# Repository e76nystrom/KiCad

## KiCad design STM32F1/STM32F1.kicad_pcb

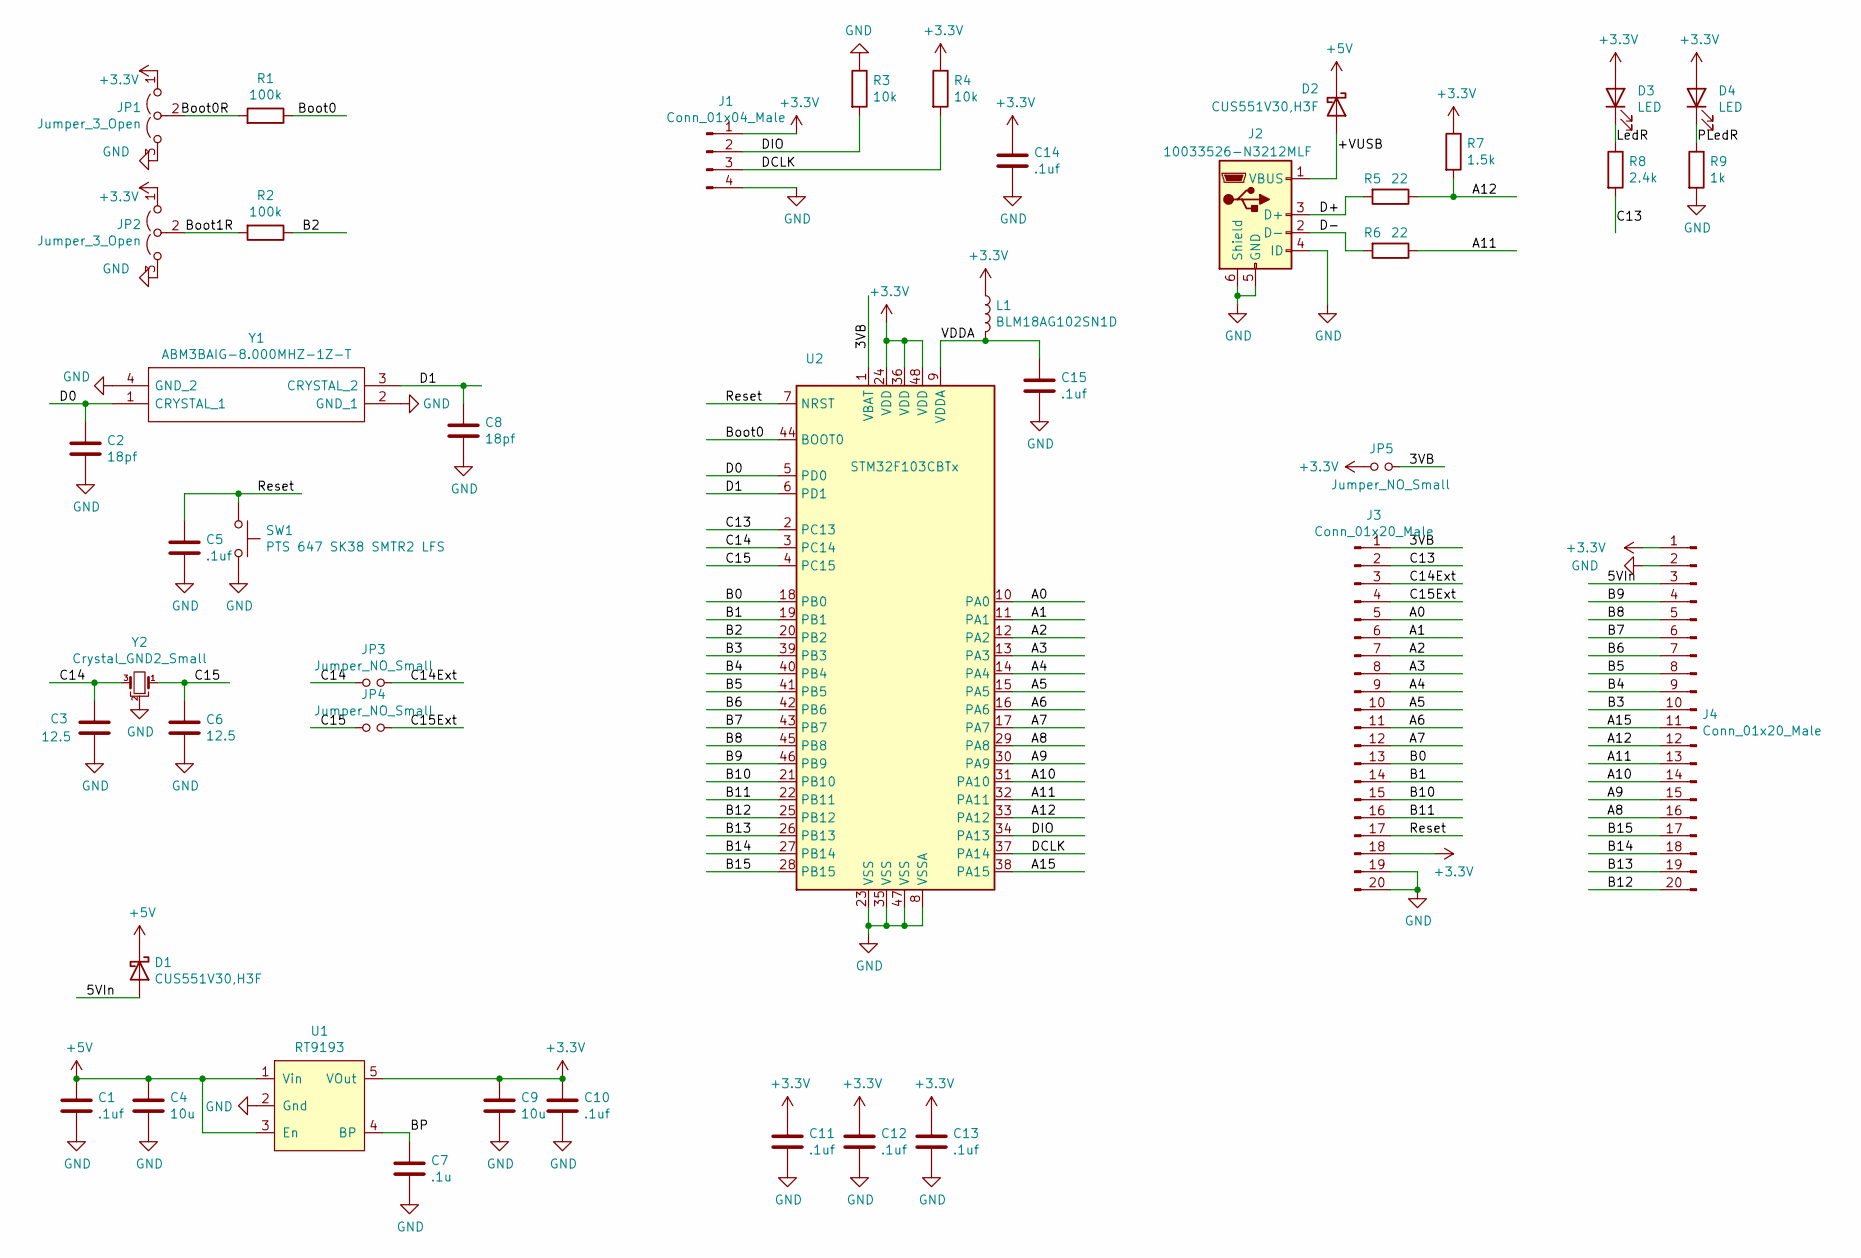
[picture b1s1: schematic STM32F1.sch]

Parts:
C1, C5, C10, C11, C12, C13, C14, C15: .1uf; C_0603_1608Metric_Pad1.05x0.95mm_HandSolder
C2, C8: 18pf; C_0603_1608Metric_Pad1.05x0.95mm_HandSolder
C3, C6: 12.5; C_0603_1608Metric_Pad1.05x0.95mm_HandSolder
C4, C9: 10u; C_0805_2012Metric_Pad1.15x1.40mm_HandSolder
C7: .1u; C_0603_1608Metric_Pad1.05x0.95mm_HandSolder
D1, D2: CUS551V30,H3F; D_SOD-323_HandSoldering
D3, D4: LED; LED_0603_1608Metric_Pad1.05x1.35mm_HandSolder
J1: Conn_01x04_Male; PinHeader_1x04_P2.54mm_Vertical
J2: 10033526-N3212MLF; USB_Mini_B
J3, J4: Conn_01x20_Male; PinHeader_1x20_P2.54mm_Vertical
JP1, JP2: Jumper_3_Open; Jumper_0603_3
JP3, JP4, JP5: Jumper_NO_Small; R_0603_1608Metric_Pad0.98x0.95mm_HandSolder
L1: BLM18AG102SN1D; L_0603_1608Metric_Pad1.05x0.95mm_HandSolder
R1, R2: 100k; R_0603_1608Metric_Pad1.05x0.95mm_HandSolder
R3, R4: 10k; R_0603_1608Metric_Pad1.05x0.95mm_HandSolder
R5, R6: 22; R_0603_1608Metric_Pad1.05x0.95mm_HandSolder
R7: 1.5k; R_0603_1608Metric_Pad1.05x0.95mm_HandSolder
R8: 2.4k; R_0603_1608Metric_Pad1.05x0.95mm_HandSolder
R9: 1k; R_0603_1608Metric_Pad1.05x0.95mm_HandSolder
SW1: PTS 647 SK38 SMTR2 LFS; PB_PTS-647
U1: RT9193; SOT-23-5_HandSoldering
U2: STM32F103CBTx; LQFP-48_7x7mm_P0.5mm
Y1: ABM3BAIG-8.000MHZ-1Z-T; Crystal_ABM3BAIG_5x3.2; Mouser Part Number 815-M3BAIG-8-1ZT
Y2: Crystal_GND2_Small; Crystal_ECX-34G

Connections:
+3V3: C9.1, C10.1, C11.1, C12.1, C13.1, C14.1, D3.2 (A), D4.2 (A), J1.1, J3.18, J4.1, JP1.1 (A), JP2.1 (A), JP5.1, L1.1, R4.1, R7.1, U1.5 (VOut), U2.24 (VDD), U2.36 (VDD), U2.48 (VDD)
+5V: C1.1, C4.1, D1.1 (K), D2.1 (K), U1.1 (Vin), U1.3 (En)
/3VB: J3.1, JP5.2, U2.1 (VBAT)
/5VIn: D1.2 (A), J4.3
/+VUSB: D2.2 (A), J2.1 (VBUS)
/A0: J3.5, U2.10 (PA0)
/A1: J3.6, U2.11 (PA1)
/A2: J3.7, U2.12 (PA2)
/A3: J3.8, U2.13 (PA3)
/A4: J3.9, U2.14 (PA4)
/A5: J3.10, U2.15 (PA5)
/A6: J3.11, U2.16 (PA6)
/A7: J3.12, U2.17 (PA7)
/A8: J4.16, U2.29 (PA8)
/A9: J4.15, U2.30 (PA9)
/A10: J4.14, U2.31 (PA10)
/A11: J4.13, R6.1, U2.32 (PA11)
/A12: J4.12, R5.1, R7.2, U2.33 (PA12)
/A15: J4.11, U2.38 (PA15)
/B0: J3.13, U2.18 (PB0)
/B1: J3.14, U2.19 (PB1)
/B2: R2.1, U2.20 (PB2)
/B3: J4.10, U2.39 (PB3)
/B4: J4.9, U2.40 (PB4)
/B5: J4.8, U2.41 (PB5)
/B6: J4.7, U2.42 (PB6)
/B7: J4.6, U2.43 (PB7)
/B8: J4.5, U2.45 (PB8)
/B9: J4.4, U2.46 (PB9)
/B10: J3.15, U2.21 (PB10)
/B11: J3.16, U2.22 (PB11)
/B12: J4.20, U2.25 (PB12)
/B13: J4.19, U2.26 (PB13)
/B14: J4.18, U2.27 (PB14)
/B15: J4.17, U2.28 (PB15)
/BP: C7.1, U1.4 (BP)
/Boot0: R1.1, U2.44 (BOOT0)
/Boot0R: JP1.2 (C), R1.2
/Boot1R: JP2.2 (C), R2.2
/C13: J3.2, R8.2, U2.2 (PC13)
/C14: C3.1, JP3.1, U2.3 (PC14), Y2.3
/C14Ext: J3.3, JP3.2
/C15: C6.1, JP4.1, U2.4 (PC15), Y2.1
/C15Ext: J3.4, JP4.2
/D0: C2.1, U2.5 (PD0), Y1.1 (CRYSTAL_1)
/D1: C8.1, U2.6 (PD1), Y1.3 (CRYSTAL_2)
/D+: J2.3 (D+), R5.2
/D-: J2.2 (D-), R6.2
/DCLK: J1.3, R4.2, U2.37 (PA14)
/DIO: J1.2, R3.2, U2.34 (PA13)
/LedR: D3.1 (K), R8.1
/PLedR: D4.1 (K), R9.1
/Reset: C5.1, J3.17, SW1.1, U2.7 (NRST)
/VDDA: C15.1, L1.2, U2.9 (VDDA)
GND: C1.2, C2.2, C3.2, C4.2, C5.2, C6.2, C7.2, C8.2, C9.2, C10.2, C11.2, C12.2, C13.2, C14.2, C15.2, J1.4, J2.4 (ID), J2.5 (GND), J2.6 (Shield), J3.19, J3.20, J4.2, JP1.3 (B), JP2.3 (B), R3.1, R9.2, SW1.2, U1.2 (Gnd), U2.8 (VSSA), U2.23 (VSS), U2.35 (VSS), U2.47 (VSS), Y1.2 (GND_1), Y1.4 (GND_2), Y2.2

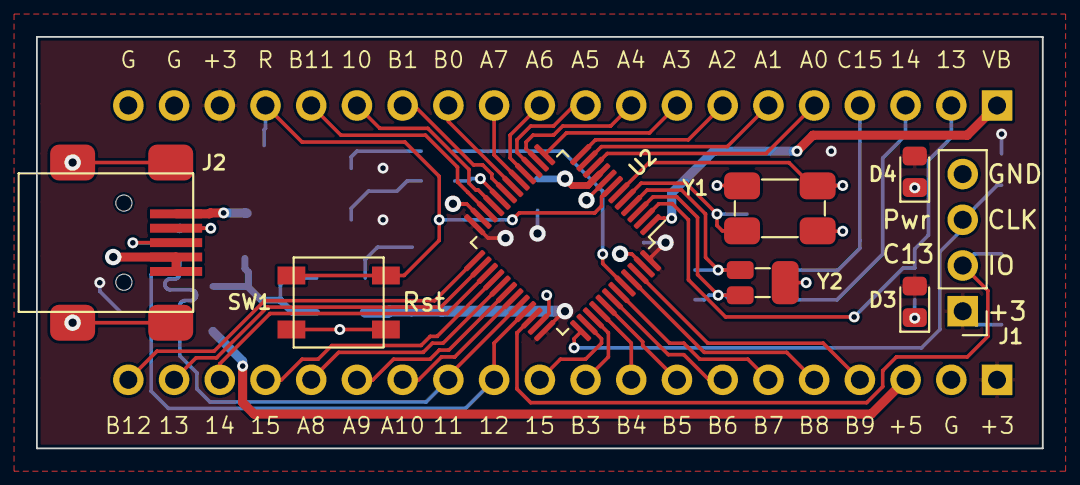
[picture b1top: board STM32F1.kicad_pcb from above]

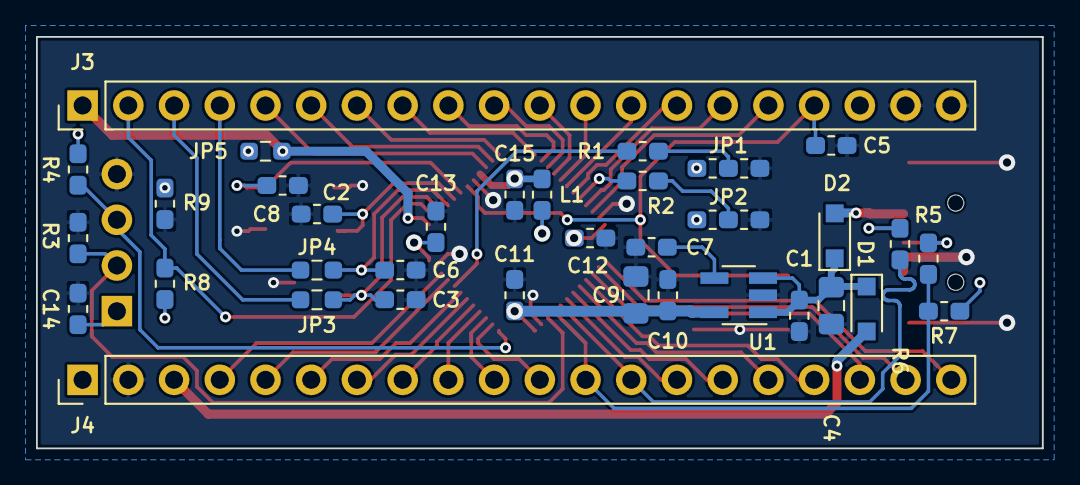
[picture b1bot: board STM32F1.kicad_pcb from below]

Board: 2 copper layers, 55.9 x 22.9 mm, 43 parts (35 on the bottom side), 55 nets.

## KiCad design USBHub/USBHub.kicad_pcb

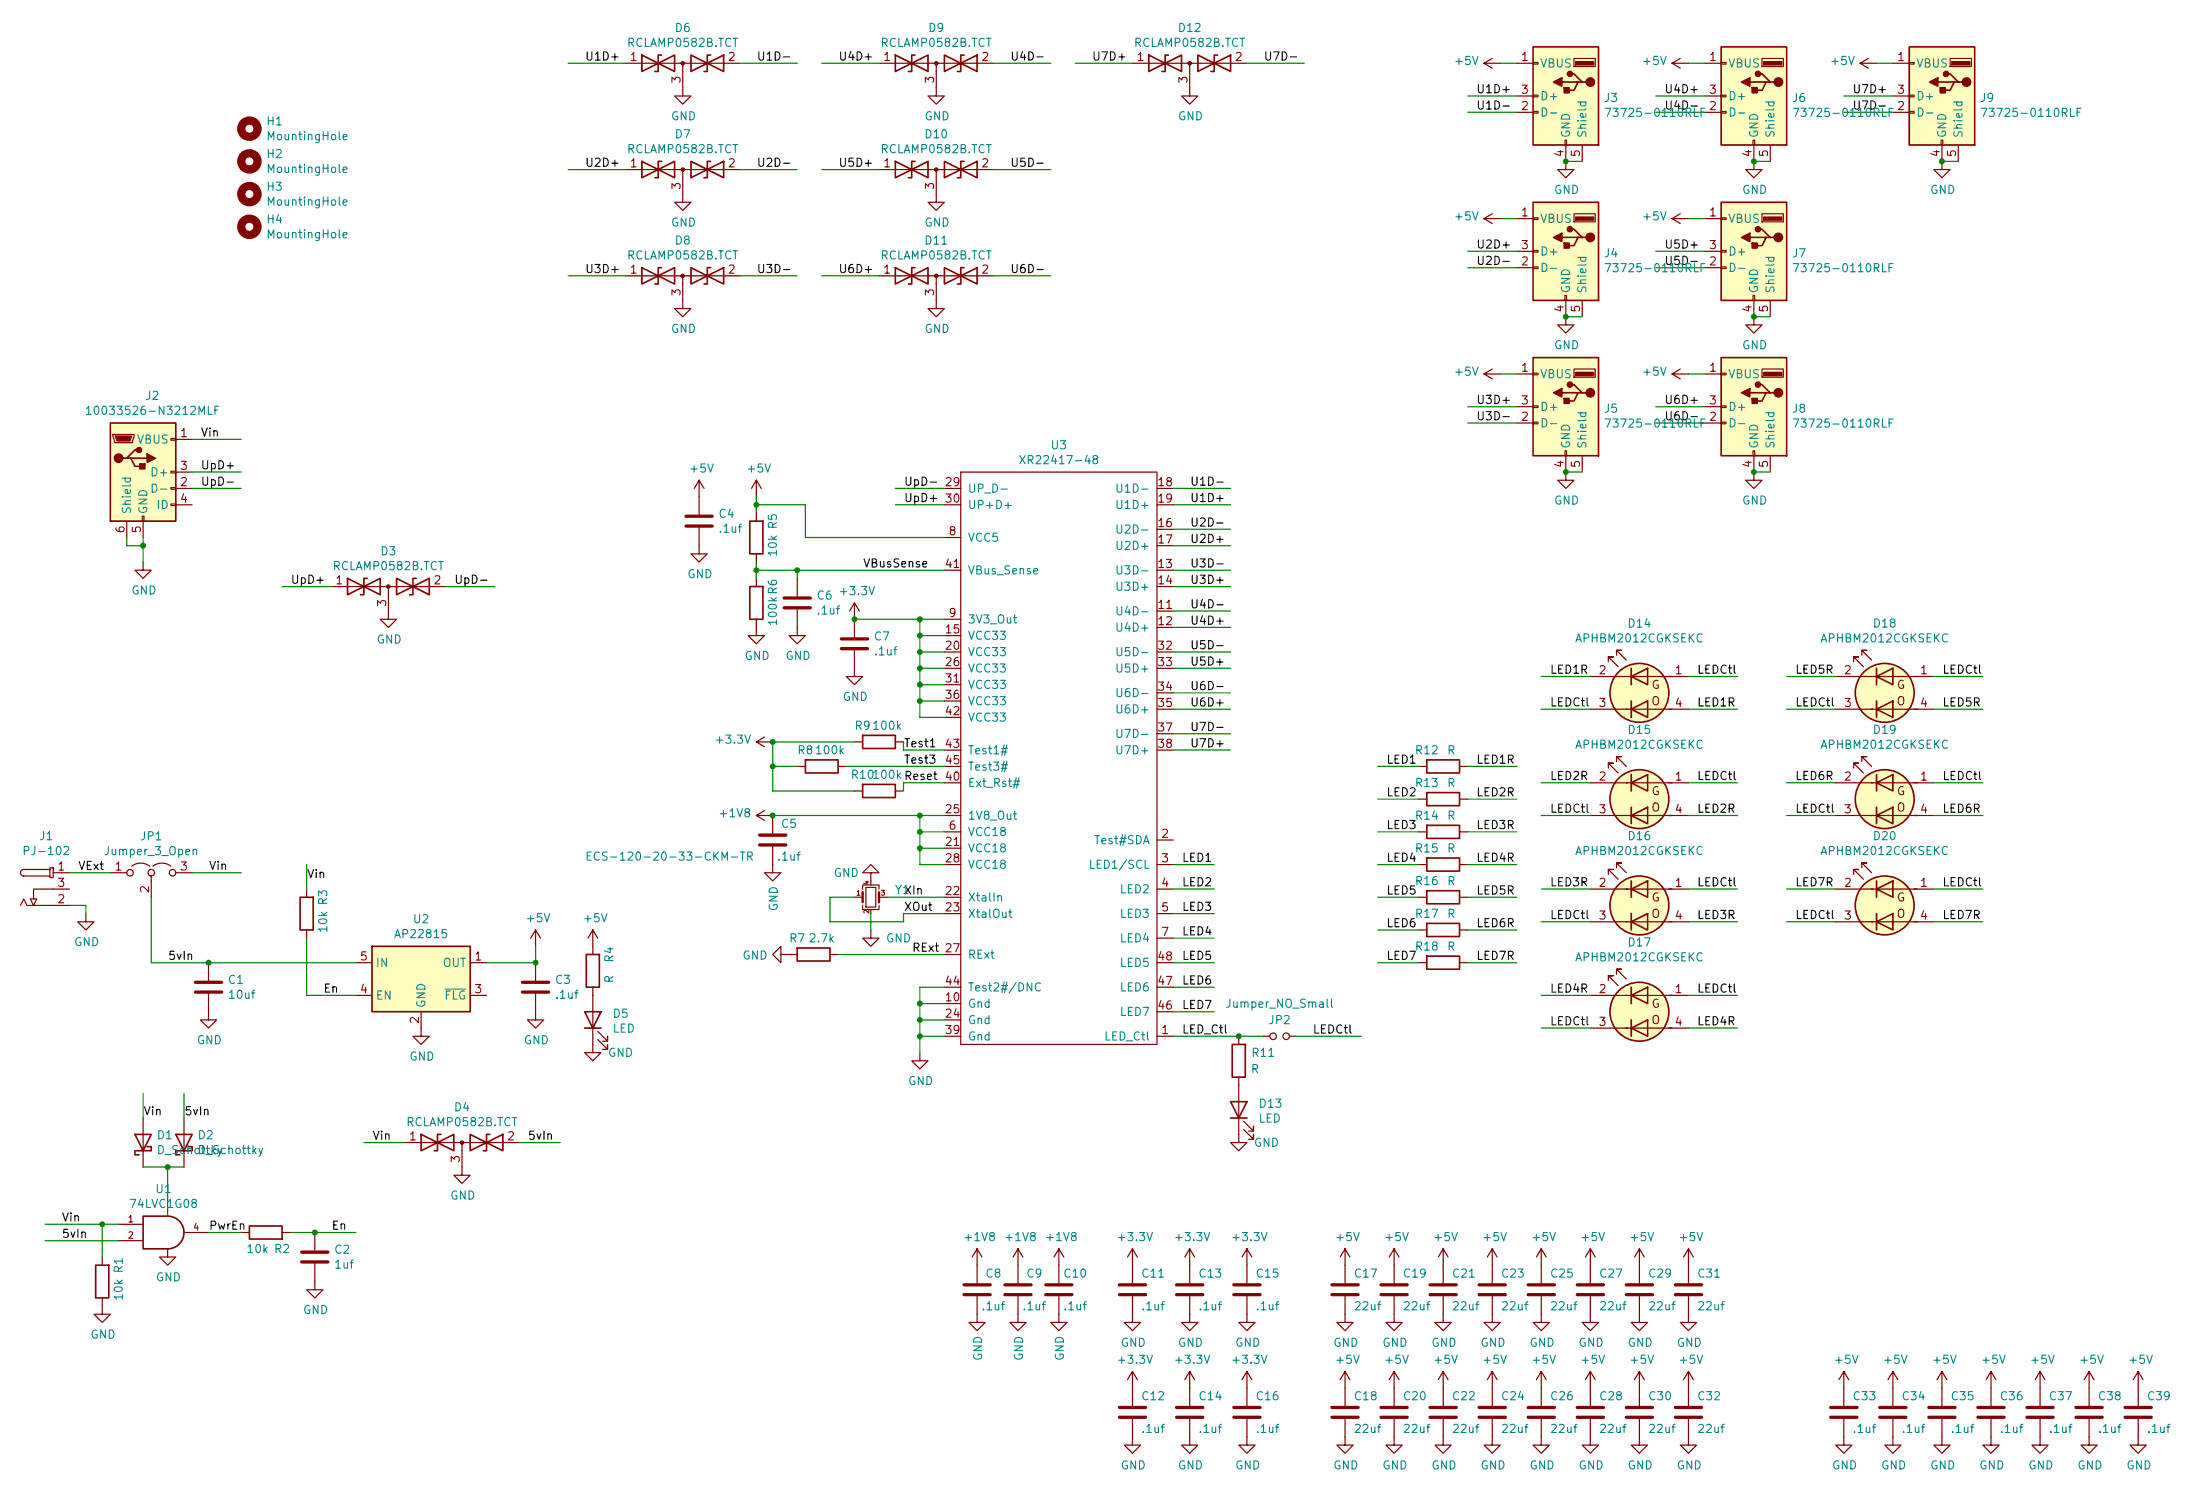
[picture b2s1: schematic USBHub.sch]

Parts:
C1: 10uf; C_0805_2012Metric_Pad1.15x1.40mm_HandSolder
C2: 1uf; C_0603_1608Metric_Pad1.05x0.95mm_HandSolder
C3, C4, C5, C6, C7, C8, C9, C10, C11, C12, C13, C14, C15, C16, C33, C34, C35, C36, C37, C38, C39: .1uf; C_0603_1608Metric_Pad1.05x0.95mm_HandSolder
C17, C18, C19, C20, C21, C22, C23, C24, C25, C26, C27, C28, C29, C30, C31, C32: 22uf; C_1206_3216Metric_Pad1.33x1.80mm_HandSolder
D1, D2: D_Schottky; D_SOD-123
D3, D4, D6, D7, D8, D9, D10, D11, D12: ‎RCLAMP0582B.TCT‎; SOT-523
D5, D13: LED; LED_0603_1608Metric_Pad1.05x1.35mm_HandSolder
D14, D15, D16, D17, D18, D19, D20: APHBM2012CGKSEKC; LED_2_2x1.25
H1, H2, H3, H4: MountingHole; MountingHole _1-8_1-4
J1: PJ-102; PJ-102-3.81mm
J2: 10033526-N3212MLF; USB_Mini_B
J3, J4, J5, J6, J7, J8, J9: 73725-0110RLF; USB_A_RA_73725
JP1: Jumper_3_Open; SolderJumper-3_P2.0mm_Open_TrianglePad1.0x1.5mm
JP2: Jumper_NO_Small; R_0603_1608Metric_Pad0.98x0.95mm_HandSolder
R1, R2, R3, R5: 10k; R_0603_1608Metric_Pad0.98x0.95mm_HandSolder
R4, R11, R12, R13, R14, R15, R16, R17, R18: R; R_0603_1608Metric_Pad0.98x0.95mm_HandSolder
R6, R8, R9, R10: 100k; R_0603_1608Metric_Pad0.98x0.95mm_HandSolder
R7: 2.7k; R_0603_1608Metric_Pad0.98x0.95mm_HandSolder
U1: 74LVC1G08; SOT-23-5_HandSoldering
U2: AP22815; SOT-23-5
U3: XR22417-48; LQFP-48_7x7mm_P0.5mm
Y1: ECS-120-20-33-CKM-TR; Crystal_SMD_3225-4Pin_3.2x2.5mm_HandSoldering

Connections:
+1V8: C5.1, C8.1, C9.1, C10.1, U3.6 (VCC18), U3.21 (VCC18), U3.25 (1V8_Out), U3.28 (VCC18)
+3V3: C7.1, C11.1, C12.1, C13.1, C14.1, C15.1, C16.1, R8.2, R9.2, R10.2, U3.9 (3V3_Out), U3.15 (VCC33), U3.20 (VCC33), U3.26 (VCC33), U3.31 (VCC33), U3.36 (VCC33), U3.42 (VCC33)
+5V: C3.1, C4.1, C17.1, C18.1, C19.1, C20.1, C21.1, C22.1, C23.1, C24.1, C25.1, C26.1, C27.1, C28.1, C29.1, C30.1, C31.1, C32.1, C33.1, C34.1, C35.1, C36.1, C37.1, C38.1, C39.1, J3.1 (VBUS), J4.1 (VBUS), J5.1 (VBUS), J6.1 (VBUS), J7.1 (VBUS), J8.1 (VBUS), J9.1 (VBUS), R4.2, R5.2, U2.1 (OUT), U3.8 (VCC5)
/5vIn: C1.1, D2.2 (A), D4.2 (A2), JP1.2 (C), U1.2, U2.5 (IN)
/En: C2.1, R2.2, R3.1, U2.4 (EN)
/LED1: R12.2, U3.3 (LED1/SCL)
/LED1R: D14.2 (K1), D14.4 (A2), R12.1
/LED2: R13.2, U3.4 (LED2)
/LED2R: D15.2 (K1), D15.4 (A2), R13.1
/LED3: R14.2, U3.5 (LED3)
/LED3R: D16.2 (K1), D16.4 (A2), R14.1
/LED4: R15.2, U3.7 (LED4)
/LED4R: D17.2 (K1), D17.4 (A2), R15.1
/LED5: R16.2, U3.48 (LED5)
/LED5R: D18.2 (K1), D18.4 (A2), R16.1
/LED6: R17.2, U3.47 (LED6)
/LED6R: D19.2 (K1), D19.4 (A2), R17.1
/LED7: R18.2, U3.46 (LED7)
/LED7R: D20.2 (K1), D20.4 (A2), R18.1
/LEDCtl: D14.1 (A1), D14.3 (K2), D15.1 (A1), D15.3 (K2), D16.1 (A1), D16.3 (K2), D17.1 (A1), D17.3 (K2), D18.1 (A1), D18.3 (K2), D19.1 (A1), D19.3 (K2), D20.1 (A1), D20.3 (K2), JP2.2
/LED_Ctl: JP2.1, R11.2, U3.1 (LED_Ctl)
/PwrEn: R2.1, U1.4
/RExt: R7.1, U3.27 (RExt)
/Reset: R10.1, U3.40 (Ext_Rst#)
/Test1: R9.1, U3.43 (Test1#)
/Test3: R8.1, U3.45 (Test3#)
/U1D+: D6.1 (A1), J3.3 (D+), U3.19 (U1D+)
/U1D-: D6.2 (A2), J3.2 (D-), U3.18 (U1D-)
/U2D+: D7.1 (A1), J4.3 (D+), U3.17 (U2D+)
/U2D-: D7.2 (A2), J4.2 (D-), U3.16 (U2D-)
/U3D+: D8.1 (A1), J5.3 (D+), U3.14 (U3D+)
/U3D-: D8.2 (A2), J5.2 (D-), U3.13 (U3D-)
/U4D+: D9.1 (A1), J6.3 (D+), U3.12 (U4D+)
/U4D-: D9.2 (A2), J6.2 (D-), U3.11 (U4D-)
/U5D+: D10.1 (A1), J7.3 (D+), U3.33 (U5D+)
/U5D-: D10.2 (A2), J7.2 (D-), U3.32 (U5D-)
/U6D+: D11.1 (A1), J8.3 (D+), U3.35 (U6D+)
/U6D-: D11.2 (A2), J8.2 (D-), U3.34 (U6D-)
/U7D+: D12.1 (A1), J9.3 (D+), U3.38 (U7D+)
/U7D-: D12.2 (A2), J9.2 (D-), U3.37 (U7D-)
/UpD+: D3.1 (A1), J2.3 (D+), U3.30 (UP+D+)
/UpD-: D3.2 (A2), J2.2 (D-), U3.29 (UP_D-)
/VBusSense: C6.1, R5.1, R6.2, U3.41 (VBus_Sense)
/VExt: J1.1, JP1.1 (A)
/Vin: D1.2 (A), D4.1 (A1), J2.1 (VBUS), JP1.3 (B), R1.2, R3.2, U1.1
/XIn: U3.22 (XtalIn), Y1.3
/XOut: U3.23 (XtalOut), Y1.1
GND: C1.2, C2.2, C3.2, C4.2, C5.2, C6.2, C7.2, C8.2, C9.2, C10.2, C11.2, C12.2, C13.2, C14.2, C15.2, C16.2, C17.2, C18.2, C19.2, C20.2, C21.2, C22.2, C23.2, C24.2, C25.2, C26.2, C27.2, C28.2, C29.2, C30.2, C31.2, C32.2, C33.2, C34.2, C35.2, C36.2, C37.2, C38.2, C39.2, D3.3 (common), D4.3 (common), D5.1 (K), D6.3 (common), D7.3 (common), D8.3 (common), D9.3 (common), D10.3 (common), D11.3 (common), D12.3 (common), D13.1 (K), J1.2, J2.5 (GND), J2.6 (Shield), J3.4 (GND), J3.5 (Shield), J4.4 (GND), J4.5 (Shield), J5.4 (GND), J5.5 (Shield), J6.4 (GND), J6.5 (Shield), J7.4 (GND), J7.5 (Shield), J8.4 (GND), J8.5 (Shield), J9.4 (GND), J9.5 (Shield), R1.1, R6.1, R7.2, U1.3 (GND), U2.2 (GND), U3.10 (Gnd), U3.24 (Gnd), U3.39 (Gnd), U3.44 (Test2#/DNC), Y1.2, Y1.4
unnamed: D5.2 (A), R4.1
unnamed: D13.2 (A), R11.1
VCC: D1.1 (K), D2.1 (K), U1.5 (VCC)

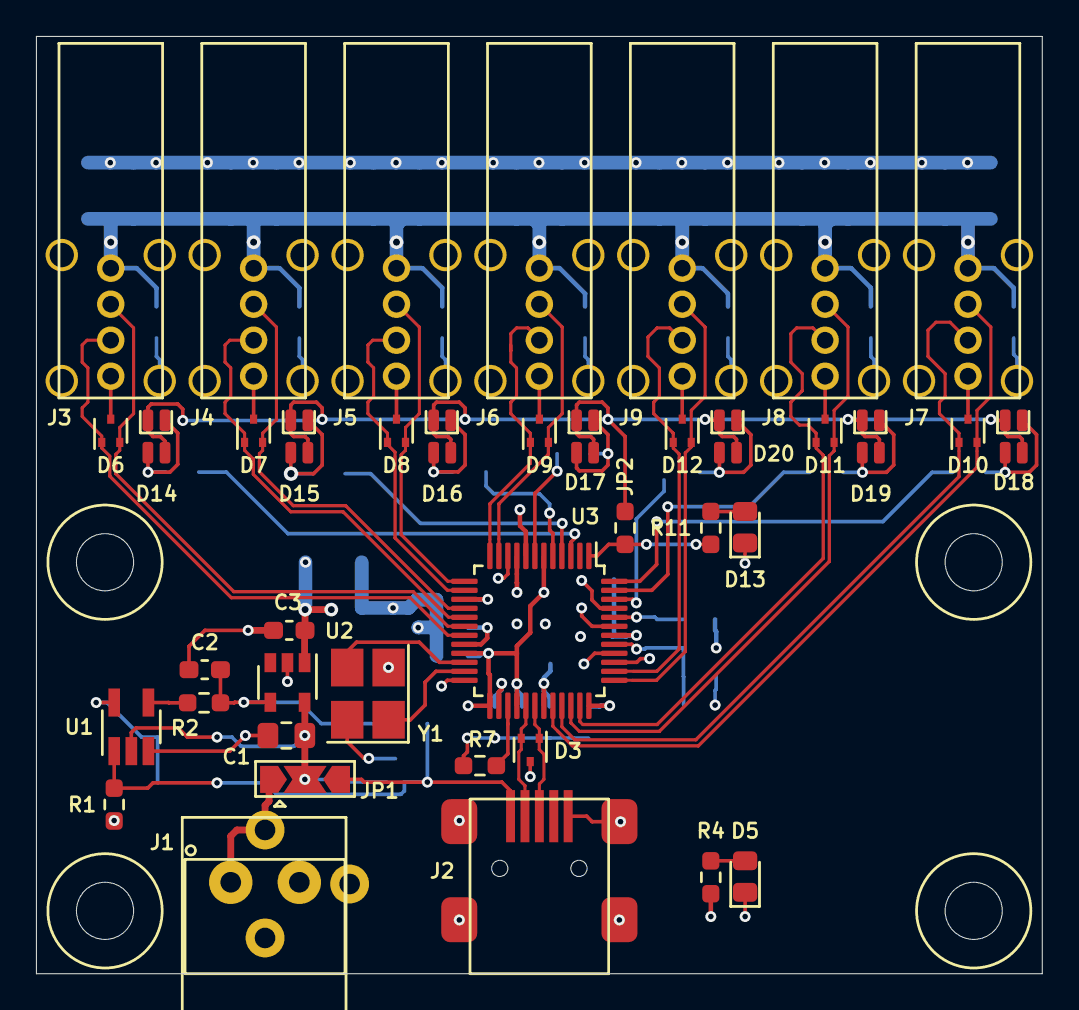
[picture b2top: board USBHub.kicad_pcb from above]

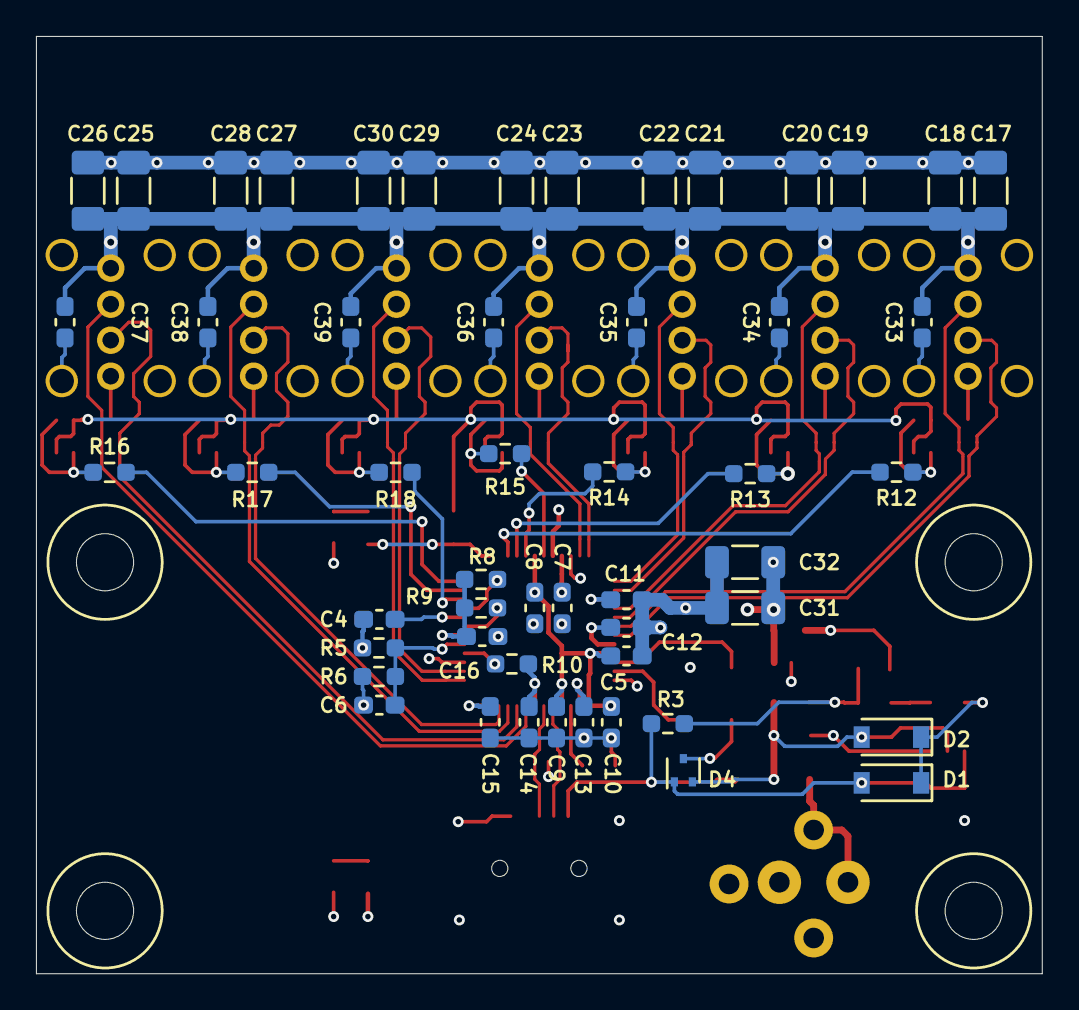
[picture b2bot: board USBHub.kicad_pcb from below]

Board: 4 copper layers, 55.9 x 52.1 mm, 96 parts (52 on the bottom side), 51 nets.

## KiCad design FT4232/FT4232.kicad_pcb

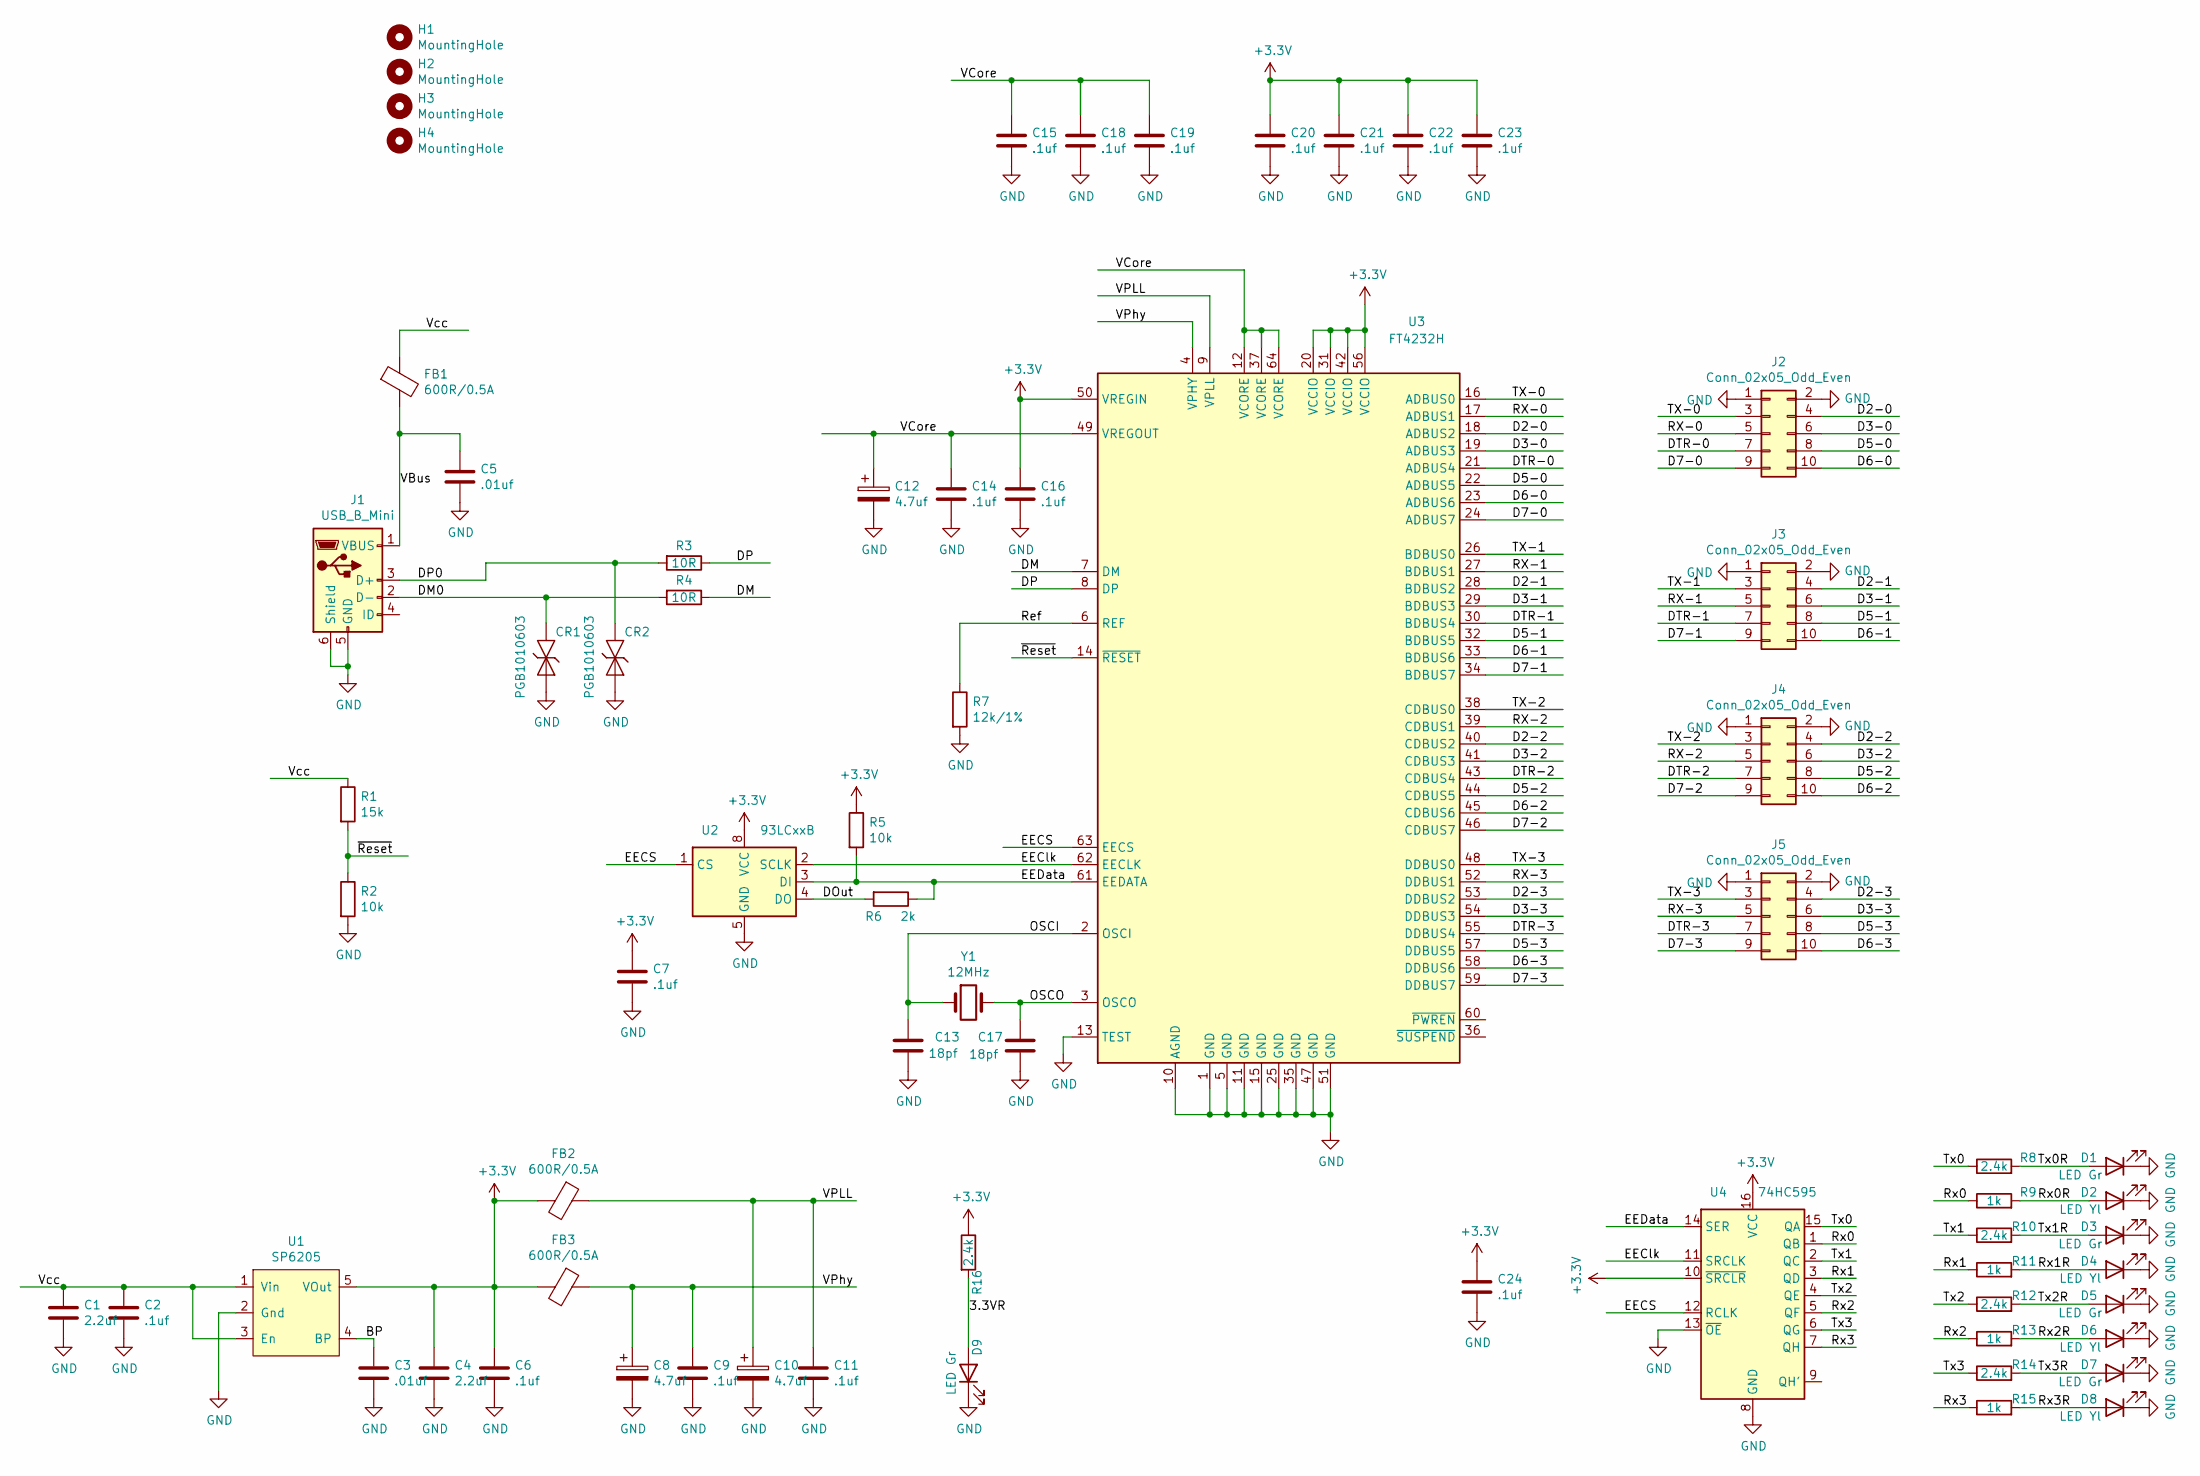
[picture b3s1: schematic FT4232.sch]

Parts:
C1, C4: 2.2uf; C_0805_2012Metric_Pad1.15x1.40mm_HandSolder
C2, C6, C7, C9, C11, C14, C15, C16, C18, C19, C20, C21, C22, C23, C24: .1uf; C_0603_1608Metric_Pad1.05x0.95mm_HandSolder
C3, C5: .01uf; C_0603_1608Metric_Pad1.05x0.95mm_HandSolder
C8, C10, C12: 4.7uf; CP_EIA-3216-18_Kemet-A_Pad1.58x1.35mm_HandSolder
C13, C17: 18pf; C_0603_1608Metric_Pad1.05x0.95mm_HandSolder
CR1, CR2: PGB1010603; R_0603_1608Metric_Pad1.05x0.95mm_HandSolder
D1, D3, D5, D7, D9: LED Gr; LED_0603_1608Metric_Pad1.05x1.35mm_HandSolder
D2, D4, D6, D8: LED Yl; LED_0603_1608Metric_Pad1.05x1.35mm_HandSolder
FB1, FB2, FB3: 600R/0.5A; L_0603_1608Metric_Pad1.05x0.95mm_HandSolder
H1, H2, H3, H4: MountingHole; MountingHole _1-8_1-4
J1: USB_B_Mini; USB_Mini_B
J2, J3, J4, J5: Conn_02x05_Odd_Even; PinHeader_2x05_P2.54mm_Vertical
R1: 15k; R_0805_2012Metric_Pad1.15x1.40mm_HandSolder
R2, R5: 10k; R_0805_2012Metric_Pad1.15x1.40mm_HandSolder
R3, R4: 10R; R_0805_2012Metric_Pad1.15x1.40mm_HandSolder
R6: 2k; R_0805_2012Metric_Pad1.15x1.40mm_HandSolder
R7: 12k/1%; R_0805_2012Metric_Pad1.15x1.40mm_HandSolder
R8, R10, R12, R14, R16: 2.4k; R_0603_1608Metric_Pad1.05x0.95mm_HandSolder
R9, R11, R13, R15: 1k; R_0603_1608Metric_Pad1.05x0.95mm_HandSolder
U1: SP6205; SOT-23-5_HandSoldering
U2: 93LCxxB; SOIC-8_3.9x4.9mm_P1.27mm
U3: FT4232H; LQFP-64_10x10mm_P0.5mm
U4: 74HC595; SOIC-16_3.9x9.9mm_P1.27mm
Y1: 12MHz; HC49_SMD

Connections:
+3V3: C4.2, C6.2, C7.2, C16.2, C20.2, C21.2, C22.2, C23.2, C24.2, FB2.2, FB3.2, R5.1, R16.1, U1.5 (VOut), U2.8 (VCC), U3.20 (VCCIO), U3.31 (VCCIO), U3.42 (VCCIO), U3.50 (VREGIN), U3.56 (VCCIO), U4.10 (~SRCLR), U4.16 (VCC)
/3.3VR: D9.2 (A), R16.2
/BP: C3.2, U1.4 (BP)
/D2-0: J2.4, U3.18 (ADBUS2)
/D2-1: J3.4, U3.28 (BDBUS2)
/D2-2: J4.4, U3.40 (CDBUS2)
/D2-3: J5.4, U3.53 (DDBUS2)
/D3-0: J2.6, U3.19 (ADBUS3)
/D3-1: J3.6, U3.29 (BDBUS3)
/D3-2: J4.6, U3.41 (CDBUS3)
/D3-3: J5.6, U3.54 (DDBUS3)
/D5-0: J2.8, U3.22 (ADBUS5)
/D5-1: J3.8, U3.32 (BDBUS5)
/D5-2: J4.8, U3.44 (CDBUS5)
/D5-3: J5.8, U3.57 (DDBUS5)
/D6-0: J2.10, U3.23 (ADBUS6)
/D6-1: J3.10, U3.33 (BDBUS6)
/D6-2: J4.10, U3.45 (CDBUS6)
/D6-3: J5.10, U3.58 (DDBUS6)
/D7-0: J2.9, U3.24 (ADBUS7)
/D7-1: J3.9, U3.34 (BDBUS7)
/D7-2: J4.9, U3.46 (CDBUS7)
/D7-3: J5.9, U3.59 (DDBUS7)
/DM: R4.1, U3.7 (DM)
/DM0: CR1.1 (K), J1.2 (D-), R4.2
/DOut: R6.2, U2.4 (DO)
/DP: R3.1, U3.8 (DP)
/DP0: CR2.1 (K), J1.3 (D+), R3.2
/DTR-0: J2.7, U3.21 (ADBUS4)
/DTR-1: J3.7, U3.30 (BDBUS4)
/DTR-2: J4.7, U3.43 (CDBUS4)
/DTR-3: J5.7, U3.55 (DDBUS4)
/EECS: U2.1 (CS), U3.63 (EECS), U4.12 (RCLK)
/EEClk: U2.2 (SCLK), U3.62 (EECLK), U4.11 (SRCLK)
/EEData: R5.2, R6.1, U2.3 (DI), U3.61 (EEDATA), U4.14 (SER)
/OSCI: C13.1, U3.2 (OSCI), Y1.1
/OSCO: C17.1, U3.3 (OSCO), Y1.2
/RX-0: J2.5, U3.17 (ADBUS1)
/RX-1: J3.5, U3.27 (BDBUS1)
/RX-2: J4.5, U3.39 (CDBUS1)
/RX-3: J5.5, U3.52 (DDBUS1)
/Ref: R7.1, U3.6 (REF)
/Rx0: R9.1, U4.1 (QB)
/Rx0R: D2.2 (A), R9.2
/Rx1: R11.1, U4.3 (QD)
/Rx1R: D4.2 (A), R11.2
/Rx2: R13.1, U4.5 (QF)
/Rx2R: D6.2 (A), R13.2
/Rx3: R15.1, U4.7 (QH)
/Rx3R: D8.2 (A), R15.2
/TX-0: J2.3, U3.16 (ADBUS0)
/TX-1: J3.3, U3.26 (BDBUS0)
/TX-2: J4.3, U3.38 (CDBUS0)
/TX-3: J5.3, U3.48 (DDBUS0)
/Tx0: R8.1, U4.15 (QA)
/Tx0R: D1.2 (A), R8.2
/Tx1: R10.1, U4.2 (QC)
/Tx1R: D3.2 (A), R10.2
/Tx2: R12.1, U4.4 (QE)
/Tx2R: D5.2 (A), R12.2
/Tx3: R14.1, U4.6 (QG)
/Tx3R: D7.2 (A), R14.2
/VBus: C5.1, FB1.2, J1.1 (VBUS)
/VCore: C12.1, C14.2, C15.2, C18.2, C19.2, U3.12 (VCORE), U3.37 (VCORE), U3.49 (VREGOUT), U3.64 (VCORE)
/VPLL: C10.1, C11.2, FB2.1, U3.9 (VPLL)
/VPhy: C8.1, C9.2, FB3.1, U3.4 (VPHY)
/Vcc: C1.2, C2.2, FB1.1, R1.1, U1.1 (Vin), U1.3 (En)
/~Reset: R1.2, R2.1, U3.14 (~RESET)
GND: C1.1, C2.1, C3.1, C4.1, C5.2, C6.1, C7.1, C8.2, C9.1, C10.2, C11.1, C12.2, C13.2, C14.1, C15.1, C16.1, C17.2, C18.1, C19.1, C20.1, C21.1, C22.1, C23.1, C24.1, CR1.2 (A), CR2.2 (A), D1.1 (K), D2.1 (K), D3.1 (K), D4.1 (K), D5.1 (K), D6.1 (K), D7.1 (K), D8.1 (K), D9.1 (K), J1.5 (GND), J1.6 (Shield), J2.1, J2.2, J3.1, J3.2, J4.1, J4.2, J5.1, J5.2, R2.2, R7.2, U1.2 (Gnd), U2.5 (GND), U3.1 (GND), U3.5 (GND), U3.10 (AGND), U3.11 (GND), U3.13 (TEST), U3.15 (GND), U3.25 (GND), U3.35 (GND), U3.47 (GND), U3.51 (GND), U4.8 (GND), U4.13 (~OE)

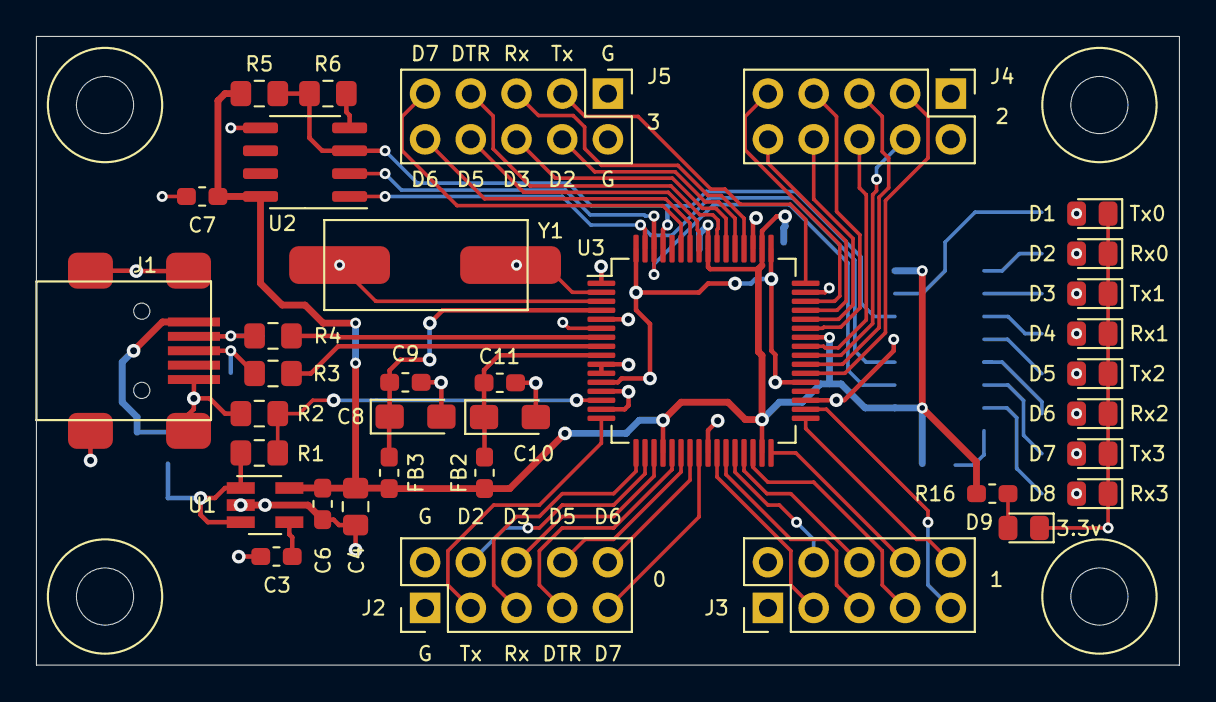
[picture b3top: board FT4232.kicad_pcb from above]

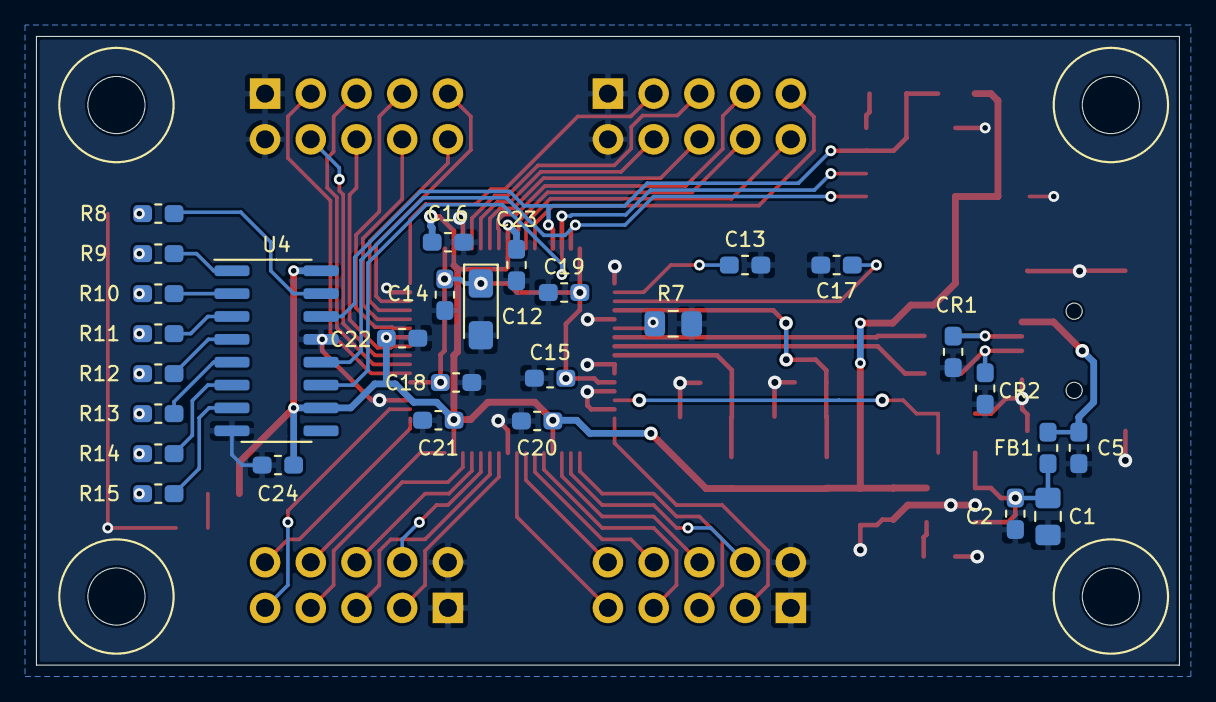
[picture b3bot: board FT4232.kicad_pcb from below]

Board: 2 copper layers, 63.5 x 34.9 mm, 68 parts (29 on the bottom side), 69 nets.
